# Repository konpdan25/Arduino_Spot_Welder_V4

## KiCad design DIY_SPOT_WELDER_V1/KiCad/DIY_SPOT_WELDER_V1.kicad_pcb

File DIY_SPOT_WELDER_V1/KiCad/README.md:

# KiCad project — DIY_SPOT_WELDER_V1

* Open `DIY_SPOT_WELDER_V1.kicad_pro` in **KiCad 10** (Windows 11).
* The files use the **KiCad 7 file format** (schematic `20230121`, PCB `20221018`), because only KiCad 7 tools were available for checking in the cloud environment. KiCad 10 opens these files natively; **save once in KiCad 10** to upgrade them, then commit.
* Libraries are self-contained: `Libraries/DIY_SPOT_WELDER_V1.kicad_sym` and `Libraries/DIY_SPOT_WELDER_V1.pretty`, referenced through the project tables `sym-lib-table` and `fp-lib-table` (`${KIPRJMOD}`). Nothing is needed from the global libraries.
* 3D models point to `${KICAD10_3DMODEL_DIR}` (variable name unverified; OI-16).
* `Generator/` regenerates the schematic, netlist checks and preliminary PCB from `Generator/design.py`. Once you edit the PCB by hand, stop using the PCB stages of `generate_all.py`.
* Schematic style: generated, so connections are made with net labels at the pin stubs (electrically explicit, checked by netlist parity). You can tidy it in KiCad without changing connectivity.
* Off-board power-assembly symbols carry *exclude from board* (`on_board no`). Do not remove that flag, or "Update PCB" will try to place the MOSFETs, relay and fuse on the control board.

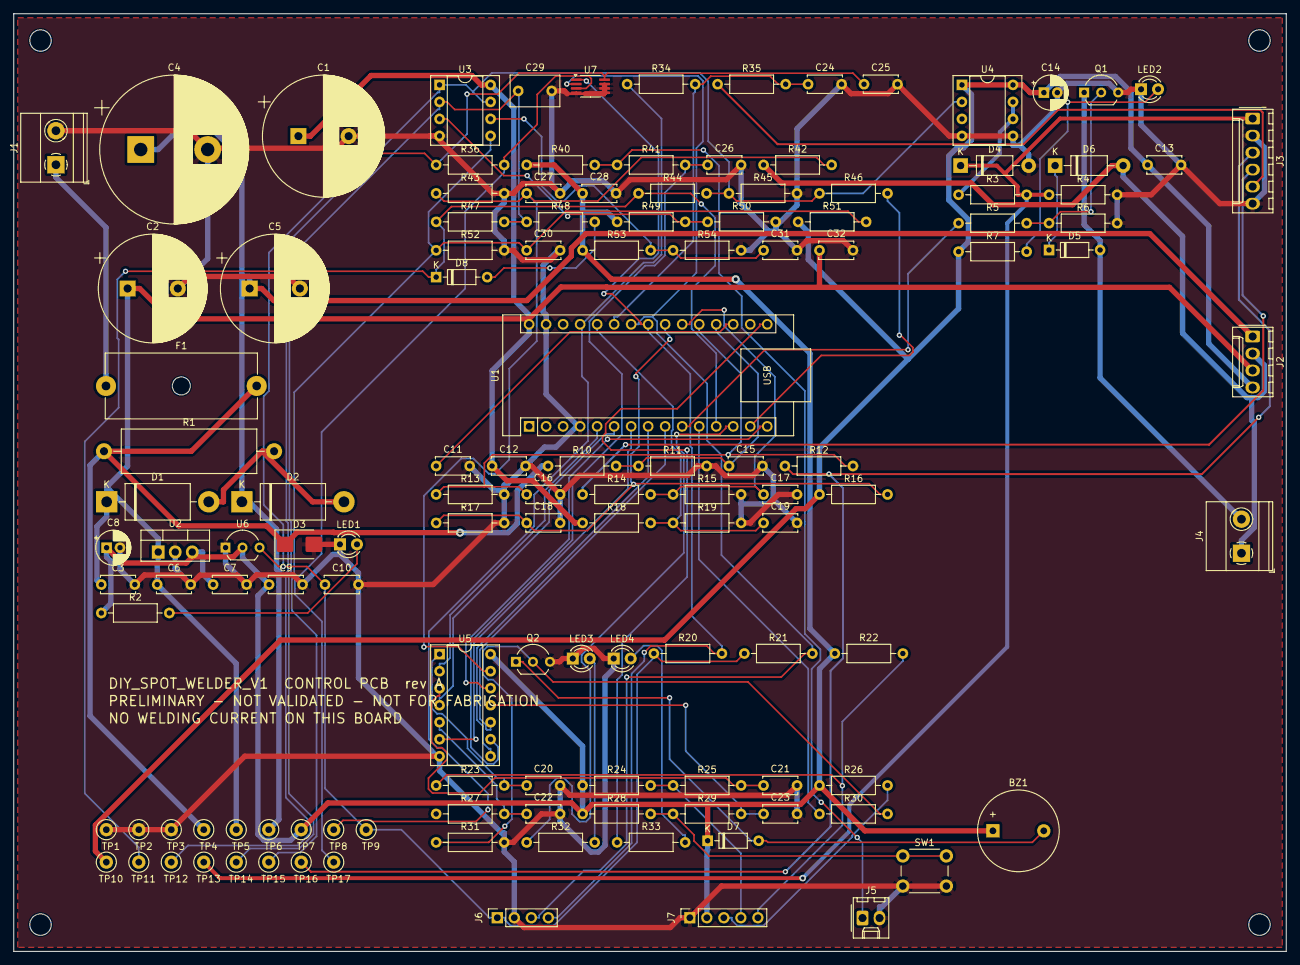
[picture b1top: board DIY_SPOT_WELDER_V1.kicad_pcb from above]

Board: 2 copper layers, 190.0 x 140.0 mm, 133 parts (0 on the bottom side), 64 nets.

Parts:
BZ1: BUZZER 5V; Buzzer_12x9.5RM7.6
C1: 6800uF; CP_Radial_D18.0mm_P7.50mm
C2: 2200uF; CP_Radial_D16.0mm_P7.50mm
C3, C7, C11, C12, C13, C15, C16, C17, C18, C19, C22, C23, C24, C25, C26, C27, C28, C30, C31, C32: 100nF; C_Disc_D5.0mm_W2.5mm_P5.00mm
C4: 10000uF; CP_Radial_D22.0mm_P10.00mm_SnapIn
C5: 4700uF; CP_Radial_D16.0mm_P7.50mm
C6: 330nF; C_Disc_D5.0mm_W2.5mm_P5.00mm
C8: 10uF; CP_Radial_D5.0mm_P2.00mm
C9, C10: 1uF; C_Disc_D5.0mm_W2.5mm_P5.00mm
C14: 47uF; CP_Radial_D5.0mm_P2.00mm
C20, C21: 10nF; C_Disc_D5.0mm_W2.5mm_P5.00mm
C29: 1uF film; C_Rect_L7.2mm_W4.5mm_P5.00mm_FKS2_FKP2_MKS2_MKP2
D1, D2: 1N5822; D_DO-201AD_P15.24mm_Horizontal
D3: SMBJ15A; D_SMB
D4, D6: BZY97C15; D_DO-41_SOD81_P10.16mm_Horizontal
D5, D7, D8: 1N4148; D_DO-35_SOD27_P7.62mm_Horizontal
F1: T3.15A; Fuseholder_Cylinder-5x20mm_Schurter_0031_8201_Horizontal_Op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
H1, H2, H3, H4: M3; MountingHole_3.2mm_M3
J1: PWR_IN; TerminalBlock_Phoenix_MKDS-1,5-2-5.08_1x02_P5.08mm_Horizont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
J2: ARM_ESTOP; Molex_KK-254_AE-6410-04A_1x04_P2.54mm_Vertical
J3: GATE_SENSE; Molex_KK-254_AE-6410-06A_1x06_P2.54mm_Vertical
J4: RELAY_COIL; TerminalBlock_Phoenix_MKDS-1,5-2-5.08_1x02_P5.08mm_Horizont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
J5: FOOT_SWITCH; Molex_KK-254_AE-6410-02A_1x02_P2.54mm_Vertical
J6: OLED; PinSocket_1x04_P2.54mm_Vertical
J7: ENCODER; PinSocket_1x05_P2.54mm_Vertical
LED1: GREEN 5V_AUX; LED_D3.0mm
LED2: YELLOW ARMED; LED_D3.0mm
LED3: RED FAULT; LED_D3.0mm
LED4: GREEN READY; LED_D3.0mm
Q1: BC337; TO-92_Inline_Wide
Q2: BC547; TO-92_Inline_Wide
R1: 1.5R 5W; R_Axial_Power_L20.0mm_W6.4mm_P25.40mm
R2, R23, R25, R27, R29, R30, R32, R33, R35, R41: 1k; R_Axial_DIN0207_L6.3mm_D2.5mm_P10.16mm_Horizontal
R3: 2.2R; R_Axial_DIN0207_L6.3mm_D2.5mm_P10.16mm_Horizontal
R4, R6, R11, R13, R15, R17, R19, R22, R24, R26, R28, R31, R34, R36, R40, R42, R46, R49, R52, R53, R54: 10k; R_Axial_DIN0207_L6.3mm_D2.5mm_P10.16mm_Horizontal
R5: 220R; R_Axial_DIN0207_L6.3mm_D2.5mm_P10.16mm_Horizontal
R7, R20, R21, R43, R48: 4.7k; R_Axial_DIN0207_L6.3mm_D2.5mm_P10.16mm_Horizontal
R10, R12, R14, R16, R18: 33k; R_Axial_DIN0207_L6.3mm_D2.5mm_P10.16mm_Horizontal
R44: 2.2k; R_Axial_DIN0207_L6.3mm_D2.5mm_P10.16mm_Horizontal
R45, R50, R51: 22k; R_Axial_DIN0207_L6.3mm_D2.5mm_P10.16mm_Horizontal
R47: 68k; R_Axial_DIN0207_L6.3mm_D2.5mm_P10.16mm_Horizontal
SW1: ACK / RESET FAULT; SW_PUSH_6mm
TP1, TP2, TP3: GND; TestPoint_Loop_D2.50mm_Drill1.0mm
TP4: VBAT_F; TestPoint_Loop_D2.50mm_Drill1.0mm
TP5: VHOLD_LOGIC; TestPoint_Loop_D2.50mm_Drill1.0mm
TP6: VHOLD_RELAY; TestPoint_Loop_D2.50mm_Drill1.0mm
TP7: +5V_AUX; TestPoint_Loop_D2.50mm_Drill1.0mm
TP8: +5V_MCU; TestPoint_Loop_D2.50mm_Drill1.0mm
TP9: +3V3; TestPoint_Loop_D2.50mm_Drill1.0mm
TP10: VDRV; TestPoint_Loop_D2.50mm_Drill1.0mm
TP11: GATE_CMD; TestPoint_Loop_D2.50mm_Drill1.0mm
TP12: GIN; TestPoint_Loop_D2.50mm_Drill1.0mm
TP13: GATE_OUT; TestPoint_Loop_D2.50mm_Drill1.0mm
TP14: PL_CT; TestPoint_Loop_D2.50mm_Drill1.0mm
TP15: UV_SENSE; TestPoint_Loop_D2.50mm_Drill1.0mm
TP16: DRAIN_BUS; TestPoint_Loop_D2.50mm_Drill1.0mm
TP17: TEMP_ALERT; TestPoint_Loop_D2.50mm_Drill1.0mm
U1: Arduino Nano V3 (ATmega328P); Arduino_Nano
U2: 7805; TO-220-3_Vertical
U3: LM393; DIP-8_W7.62mm_Socket
U4: TC4422CPA; DIP-8_W7.62mm_Socket
U5: 74HCT14; DIP-14_W7.62mm_Socket
U6: MCP1700-3302E/TO; TO-92_Inline_Wide
U7: MCP9804; MSOP-8_3x3mm_P0.65mm

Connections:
+3V3: C10.1, C25.1, J6.1, R20.1, R21.1, R36.1, TP9.1, U6.3, U7.8
+5V_AUX: BZ1.1, C7.1, C8.1, C9.1, C28.1, D7.1, J7.2, R2.1, R22.1, R24.1, R26.1, R28.1, R40.1, R49.1, R53.1, TP7.1, U2.3, U5.14, U6.2
+5V_MCU: R34.1, TP8.1, U1.27
ACK_ACT: U1.9, U5.10
ACK_RAW: R28.2, R29.1, SW1.1
ACK_RAW_F: C23.1, R29.2, U5.11
ADC_NTC: C24.1, R34.2, R35.2, U1.25
ADC_VBAT: C15.1, R10.2, R11.1, U1.19
ADC_VDRAIN: C16.1, R12.2, R13.1, U1.20
ADC_VDRV: C18.1, R16.2, R17.1, U1.22
ADC_VELEC: C17.1, R14.2, R15.1, U1.21
ADC_VHOLD: C19.1, R18.2, R19.1, U1.26
AREF: C11.1, U1.18
ARM_A_DIV: C27.1, R42.2, R43.1, U5.13
ARM_A_N: U1.15, U5.12
BUZZER_CMD: R30.1, U1.11
BZ_N: BZ1.2, D7.2, Q2.1
D5_K: D5.1, D6.1
DRAIN_BUS: J3.3, R12.1, TP16.1
ELEC_POS: J3.4, R14.1
ENC_A: U1.5, U5.2
ENC_A_RAW: J7.5, R22.2, R23.1
ENC_A_RAW_F: C20.1, R23.2, U5.1
ENC_B: U1.6, U5.4
ENC_B_RAW: J7.4, R24.2, R25.1
ENC_B_RAW_F: C21.1, R25.2, U5.3
ENC_SW: U1.7, U5.6
ENC_SW_RAW: J7.3, R26.2, R27.1
ENC_SW_RAW_F: C22.1, R27.2, U5.5
FOOT_ACT: U1.8, U5.8
FOOT_RAW: J5.1, R40.2, R41.1
FOOT_RAW_F: C26.1, R41.2, U5.9
GATE_CMD: D8.1, R44.1, R47.1, TP11.1, U1.12
GATE_DRV: R3.1, U4.6, U4.7
GATE_FB: R46.2, U1.14
GATE_OUT: D4.1, J3.1, R3.2, R4.1, TP13.1
GIN: R44.2, R45.1, R46.1, TP12.1, U3.1, U3.7, U4.2
GND: C1.2, C2.2, C3.2, C4.2, C5.2, C6.2, C7.2, C8.2, C9.2, C10.2, C11.2, C12.2, C13.2, C14.2, C15.2, C16.2, C17.2, C18.2, C19.2, C20.2, C21.2, C22.2, C23.2, C24.2, C25.2, C26.2, C27.2, C28.2, C29.2, C30.2, C31.2, C32.2, D3.2, D4.2, J1.2, J3.2, J3.6, J5.2, J6.2, J7.1, LED1.1, LED2.1, LED3.1, LED4.1, Q1.3, Q2.3, R4.2, R6.2, R11.2, R13.2, R15.2, R17.2, R19.2, R31.2, R43.2, R45.2, R50.2, R52.2, R54.2, SW1.2, TP1.1, TP2.1, TP3.1, U1.4, U1.29, U2.2, U3.4, U4.4, U4.5, U5.7, U6.1, U7.4, U7.5, U7.6, U7.7
LED1_A: LED1.2, R2.2
LED2_A: LED2.2, R7.2
LED3_A: LED3.2, R32.2
LED4_A: LED4.2, R33.2
LED_FAULT_CMD: R32.1, U1.13
LED_READY_CMD: R33.1, U1.16
NTC_HS: J3.5, R35.1
PL_CT: C29.1, R47.2, R48.1, TP14.1, U3.2
PL_DIS: D8.2, R48.2
PL_VTH: R49.2, R50.1, U3.3
Q1_B: Q1.2, R5.2, R6.1
Q2_B: Q2.2, R30.2, R31.1
RELAY_COIL_N: D5.2, J4.2, Q1.1
RELAY_EN: R5.1, U1.10
SCL: J6.3, R21.2, U1.24, U7.2
SDA: J6.4, R20.2, U1.23, U7.1
TEMP_ALERT: R36.2, TP17.1, U7.3
UV_SENSE: C30.1, R51.2, R52.1, TP15.1, U3.5
VBAT_F: D3.1, F1.2, R1.1, R10.1, TP4.1
VBAT_IN: F1.1, J1.1
VDRV: C13.1, C14.1, J2.4, R7.1, R16.1, R51.1, TP10.1, U4.1, U4.8
VHOLD_LOGIC: C1.1, C2.1, C3.1, C6.1, C12.1, C32.1, D1.1, J2.3, R18.1, TP5.1, U1.30, U2.1, U3.8
VHOLD_RELAY: C4.1, C5.1, D2.1, J2.1, TP6.1
VREF_2V5: C31.1, R53.2, R54.1, U3.6
VRELAY_ARM: D6.2, J2.2, J4.1, R42.1
VTAP: D1.2, D2.2, R1.2

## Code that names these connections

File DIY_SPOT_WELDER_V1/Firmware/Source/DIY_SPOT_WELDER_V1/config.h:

// SPDX-License-Identifier: GPL-3.0-or-later
// DIY_SPOT_WELDER_V1 firmware - configuration (pins, limits, thresholds)
//
// Concepts (double pulse, contact-triggered pulse) follow the Arduino Spot Welder V4 by
// Marc Schoenfleisch / Malectrics (GPL-3.0). This file is new code.
#pragma once
#include <stdint.h>

#define FW_NAME     "DIY_SPOT_WELDER_V1"
#define FW_VERSION  "0.1.0-prelim"

// ---------------------------------------------------------------------------
// Pin map (Arduino Nano, see KiCad sheet 03). All inputs from 74HCT14 are ACTIVE HIGH
// except ARM_A_N (low = relay pole of the ARM chain closed).
// ---------------------------------------------------------------------------
#define PIN_ENC_A        2   // INT0
#define PIN_ENC_B        3   // INT1
#define PIN_ENC_SW       4
#define PIN_FOOT         5
#define PIN_ACK          6
#define PIN_RELAY_EN     7
#define PIN_BUZZER       8
#define PIN_GATE_CMD     9   // PB1 / OC1A - weld pulse command (hardware pull-down R45)
#define PIN_LED_FAULT    10
#define PIN_GATE_FB      11  // effective TC4422 input (after wired-AND limiter/UVLO)
#define PIN_ARM_A_N      12
#define PIN_LED_READY    13
#define PIN_ADC_VBAT     A0
#define PIN_ADC_VDRAIN   A1
#define PIN_ADC_VELEC    A2
#define PIN_ADC_VDRV     A3
#define PIN_ADC_NTC      A6
#define PIN_ADC_VHOLD    A7

// ---------------------------------------------------------------------------
// Analog scaling: 33k/10k dividers -> k = 4.3, ADC ref = AVCC (Nano 5 V)
// ---------------------------------------------------------------------------
#define ADC_DIVIDER_NUM   43     // k = 43/10
#define ADC_DIVIDER_DEN   10
#define ADC_VREF_MV       5000   // calibrate per board (cal factor in settings)

// ---------------------------------------------------------------------------
// Pulse limits. HARD limits are compile-time and cannot be exceeded from the menu.
// Hardware limiter window: 63..96 ms per ON interval (doc 03 section 8).
// MOSFET thermal limit: ~53 ms at ~300 A, Tcase 50 C (doc 03 section 4).
// ---------------------------------------------------------------------------
#define HARD_MAX_MAIN_US      50000UL   // 50 ms
#define HARD_MIN_MAIN_US      1000UL    // 1 ms
#define HARD_MAX_PRE_PCT      30        // pre-pulse <= 30 % of main
#define HARD_MAX_TOTAL_ON_US  65000UL   // pre + main
#define HARD_MIN_GAP_US       2000UL    // gap >= 2 ms (limiter capacitor partly discharges)
#define HARD_MAX_GAP_US       50000UL
#define SEQ_GUARD_MS          20        // extra time before the core declares a sequencer fault

// ---------------------------------------------------------------------------
// Trigger
// ---------------------------------------------------------------------------
#define DEBOUNCE_MS              30
#define MIN_TRIGGER_DELAY_MS     150     // foot switch must be held this long (continuously)
#define MAX_TRIGGER_DELAY_MS     2000
#define MIN_AUTO_DELAY_MS        500     // contact must persist this long in AUTO mode
#define MAX_AUTO_DELAY_MS        5000
#define RETRIGGER_DELAY_MS       500
#define DUTY_FACTOR              20      // minimum interval = 20 x total ON time (5 % duty)

// ---------------------------------------------------------------------------
// Supervision thresholds (millivolts / deci-degC)
// ---------------------------------------------------------------------------
#define VBAT_UV_MV          11500   // below: undervoltage (RT1270 rested 12.6-12.9 V)
#define VBAT_OV_MV          14800   // above: overvoltage (charger connected?) - TC4422 VDD / VGS margin
#define VBAT_PRESENT_MV     5000    // above: P_BUS considered live
#define VDRV_OK_MV          9000    // firmware threshold (hardware UVLO trips at 8.0 V)
#define VHOLD_OK_MV         9500
#define VELEC_CLOSED_FRAC   80      // relay closed if VELEC >= 80 % of VBAT
#define VELEC_OPEN_MV       1500    // relay open if VELEC <= 1.5 V
#define CONTACT_FRAC        50      // AUTO: electrodes on workpiece if VDRAIN >= 50 % VBAT
#define STUCK_SAG_MV        1500    // idle VBAT drop vs. filtered value -> current is flowing
#define T_HS_DERATE_START_DC 400    // 40.0 C start derating
#define T_HS_LIMIT_DC        600    // 60.0 C lockout (latched)
#define T_HS_RESUME_DC       500    // 50.0 C may acknowledge
#define T_HS_MIN_VALID_DC   -300    // NTC open/short detection
#define T_HS_MAX_VALID_DC    1500
#define DERATED_MIN_MAIN_US  20000UL // at T_HS_LIMIT

// ---------------------------------------------------------------------------
// Self-test of the hardware pulse limiter during ARMING (relay OPEN -> no current possible)
// ---------------------------------------------------------------------------
#define LIMTEST_FB_RISE_MS   3       // GATE_FB must follow GATE_CMD within 3 ms
#define LIMTEST_MIN_MS       50      // limiter must not trip earlier (would truncate welds)
#define LIMTEST_MAX_MS       120     // ...and must trip before this
#define LIMTEST_RECOVER_MS   60      // let the timing capacitor discharge
#define RELAY_SETTLE_MS      80      // relay operate + bounce (unknown relay: measure!)

#define WDT_TIMEOUT_CODE     WDTO_250MS
#define STANDBY_MS           300000UL  // 5 min inactivity -> disarm relay

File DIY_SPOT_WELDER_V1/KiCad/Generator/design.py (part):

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Edit here, then run `python3 generate_all.py`.

Conventions
  * Net names are global (GND, VHOLD_LOGIC, ...). Inter-sheet connections are global labels.
  * on_board=False marks parts of the external POWER ASSEMBLY (busbars, MOSFETs, relay, fuse,
    switches, battery). They are in the schematic for completeness but are NOT placed on the
    control PCB (KiCad symbol attribute "exclude from board").
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     spec="VDD 4.5-18 V, 9 A peak, TTL/CMOS input (VIH 2.4 V), 300 mV hysteresis",
     ds="https://ww1.microchip.com/downloads/en/DeviceDoc/20001420F.pdf",
     notes="Non-inverting => input pull-down gives OFF by default. TC4421 (inverting) is REJECTED for this function.")
C("C13", "100nF", "VDRV", "GND", S4, notes="Place at U4 pins 1/8 - 4/5")
CP("C14", "47uF", "VDRV", "GND", S4, FP["CP5"], status="PURCHASE", spec="25 V low-ESR electrolytic", price="0.10",
   notes="Local reservoir for gate-charge pulses (~0.5 uC)")
R("R3", "2.2R", "GATE_DRV", "GATE_OUT", S4, notes="Common gate resistor: damps cable ringing, limits clamp current", status="PURCHASE")
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     "NTC 10 k on the drain bar (electrically insulated!)", spec="10 k @25 C, B ~3950 (verify from stock)",
     notes="Drain bar is at electrode potential: bond the NTC with Kapton + thermal epoxy; never connect to the bar.",
     on_board=False)
part("E1", "Connector:Conn_01x01_Pin", "ELECTRODE+", "", S4, {"1": "ELEC_POS"}, "PURCHASE",
     "Positive welding cable + copper electrode (16 mm2, 0.5 m)", on_board=False)
part("E2", "Connector:Conn_01x01_Pin", "ELECTRODE-", "", S4, {"1": "DRAIN_BUS"}, "PURCHASE",
     "Negative welding cable + copper electrode (16 mm2, 0.5 m), bolted to the drain bar", on_board=False)

# ===========================================================================
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     "NPN 45 V 800 mA - relay coil low-side switch", mfr="various", mpn="BC337-40",
     spec="VCEO 45 V, IC 800 mA, TO-92 C-B-E", ds="https://www.onsemi.com/pdf/datasheet/bc337-d.pdf")
R("R5", "220R", "RELAY_EN", "Q1_B", S5, notes="Base drive ~19 mA from D7 (forced beta ~16 at 300 mA)")
R("R6", "10k", "Q1_B", "GND", S5, notes="Keeps Q1 off while the MCU is in reset (pins hi-Z)")
part("D5", "Diode:1N4148", "1N4148", FP["D35"], S5, {"1": "D5_K", "2": "RELAY_COIL_N"}, "STOCK",
     "Coil clamp diode (in series with D6 zener for fast release)", mfr="various", mpn="1N4148",
     spec="100 V, IFRM 450 mA", ds="https://www.vishay.com/docs/81857/1n4148.pdf")
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    R(rs, "1k", raw, raw + "_F", S7, notes="series / RC filter")
    C(cf, cval, raw + "_F", "GND", S7)
COMPONENTS.append(dict(ref="U5", sym="74xx:74HC14", value="74HCT14", fp=FP["DIP14"], sheet=S7,
                       pins={"1": "ENC_A_RAW_F", "2": "ENC_A", "3": "ENC_B_RAW_F", "4": "ENC_B",
                             "5": "ENC_SW_RAW_F", "6": "ENC_SW", "11": "ACK_RAW_F", "10": "ACK_ACT",
                             "9": "FOOT_RAW_F", "8": "FOOT_ACT", "13": "ARM_A_DIV", "12": "ARM_A_N",
                             "14": "+5V_AUX", "7": "GND"},
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R("R54", "10k", "VREF_2V5", "GND", S9)
C("C31", "100nF", "VREF_2V5", "GND", S9)
COMPONENTS.append(dict(ref="U3", sym="Comparator:LM393", value="LM393", fp=FP["DIP8"], sheet=S9,
                       pins={"1": "GIN", "2": "PL_CT", "3": "PL_VTH",
                             "7": "GIN", "6": "VREF_2V5", "5": "UV_SENSE",
                             "8": "VHOLD_LOGIC", "4": "GND"},
                       unit_sheets={1: S9, 2: S9, 3: S9},
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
